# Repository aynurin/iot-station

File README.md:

# Nour Eggboard

This is a main board of a low-power battery powered IoT device controller based on ESP8266 (ESP-WROOM-02) that drives peripheral devices on I2C bus.

Currenly the project is under development and you can help in the following way:

* Suggest new features and report bugs
* Submit pull requests
* Help fund the development by [donating via PayPal](https://www.paypal.com/donate?business=M5DEYMX2BZ4MJ&no_recurring=0&item_name=Help+support+Nour+Eggboard+development&currency_code=USD)

## LICENSE

Currently this project is licensed as  [GNU AGPLv3](./LICENSE). This is intended to be changed to Apache or MIT when I get a better feel of the project and see how it moves forward. I would accept suggestions of a qualified lawyer as I need help figuring out how to move forward.

## How is this helpful

Most prototyping boards are exactly what they say - designed for prototyping and difficult to apply in a production device or if you are a hardcore hobbyist. Unlike those projects, the Eggboard is intended to be a final solution that lets you hook your peripherals to an I2C bus and enjoy a low-power battery operation, wireless charging, and WiFi connectivity out of the box.

Features:

* WiFi capability via ESP8266
* Own I2C port that allows I2C communication, sleep power line, ability to operate when host sleeps, and a host wakeup channel
* Customizable (via resistance change) sleep timer that drives the host and all of the peripherals
* Battery operation
* Wireless and USB-C charging
* USB-C programming via esptool or Arduino IDE (and other compatible IDEs and methods)

## Nour Egg Plant station

The example implementation is a Nour Egg plant ecosystem controller that is under development. This device is going to be commercially available for purchase in 2022 along with free downloadable app and a cloud-based analytics platform.

Key features of the Nour Egg:

* Monitor air quality, soil moisture, and lighting conditions of your home plant
* Low-power operation that runs for months on a single charge, and wireless charging
* WiFi connectivity to report statistics to the cloud and Nour Egg app
* Appealing look and feel in a nice shell and beautiful RGB light indicators

Implemented peripherals:

* Soil moisture sensor based on capacitance sensing using a coplanar capacitor probe
* Air quality sensor
* Light sensor
* LED indicators board driving 18 leds or 6 RGB leds

## Roadmap

The versioning works by bird names, e.g. see [WhatBird.com NA Birds by Size](https://www.whatbird.com/browse/attribute/birds_na_147/51/Size/):

| Milestone | Release Date | Focus |
|---|---|---|
| [Pine Siskin](https://github.com/aynurin/iot-station/milestone/1) | September 2021 | Hardware design |
| [Pygmy Nuthatch](https://github.com/aynurin/iot-station/milestone/2) | December 2021 | PoC Cloud and App |
| [Winter Wren](https://github.com/aynurin/iot-station/milestone/3) | March 2022 | Production feasible enclosure |
| [Hutton's Vireo](https://github.com/aynurin/iot-station/milestone/4) | June 2022 | Production feasible hardware, test board production |
.

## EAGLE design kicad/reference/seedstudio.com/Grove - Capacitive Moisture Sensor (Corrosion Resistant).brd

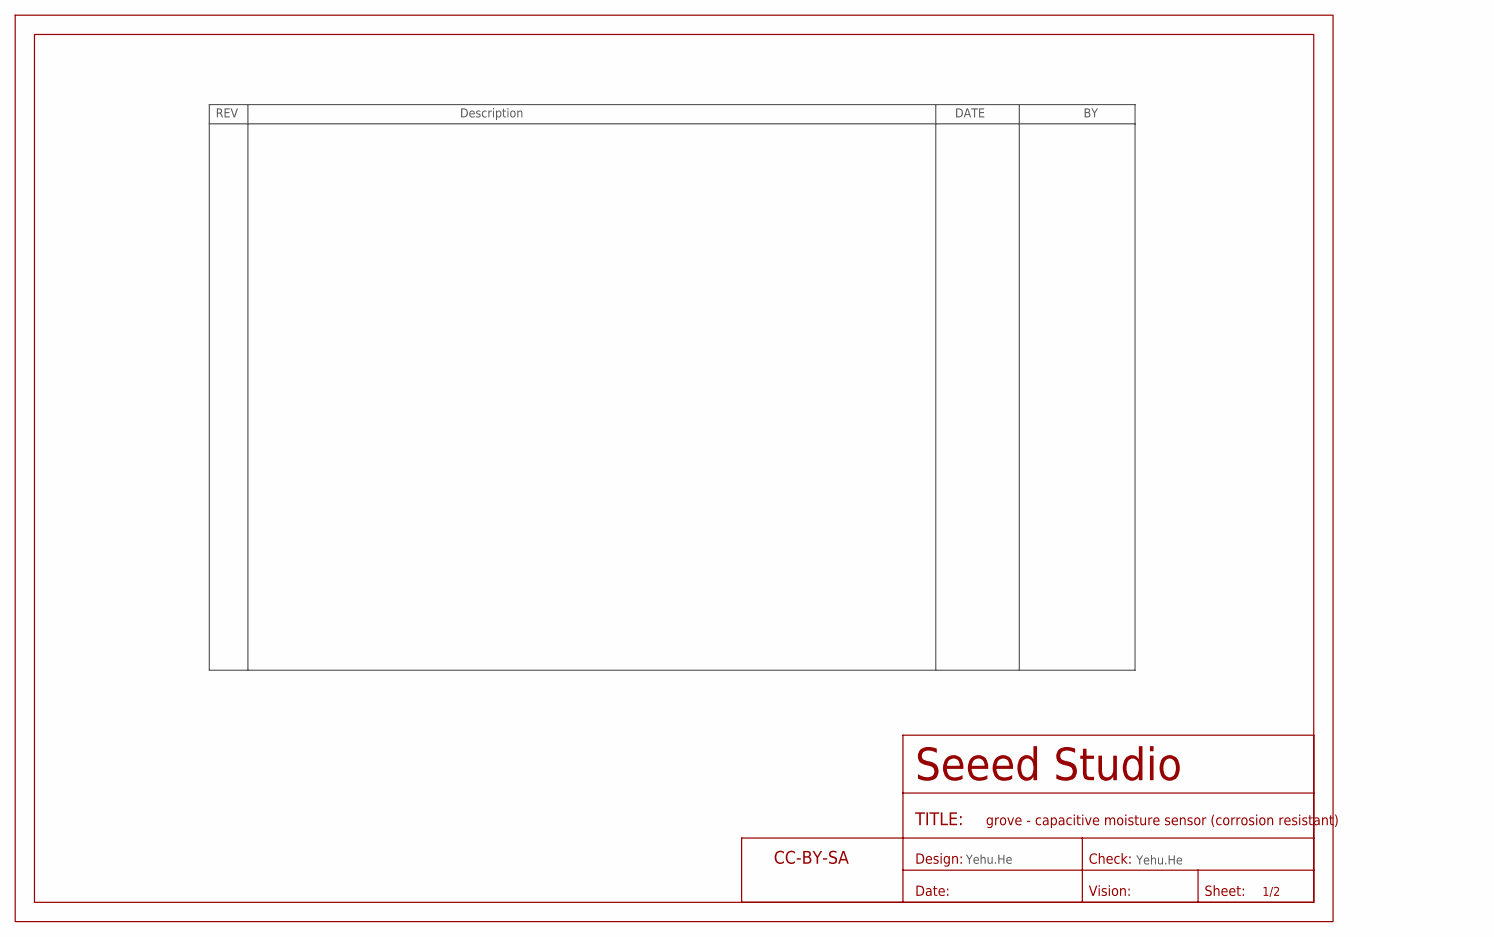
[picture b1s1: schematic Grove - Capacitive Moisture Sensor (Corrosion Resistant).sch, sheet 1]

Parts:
FR1: SEEEDSTUDIO-OPEN-SCH-FRAME; SEEEDSTUDIO-PCB-FRAME

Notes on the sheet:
Yehu.He

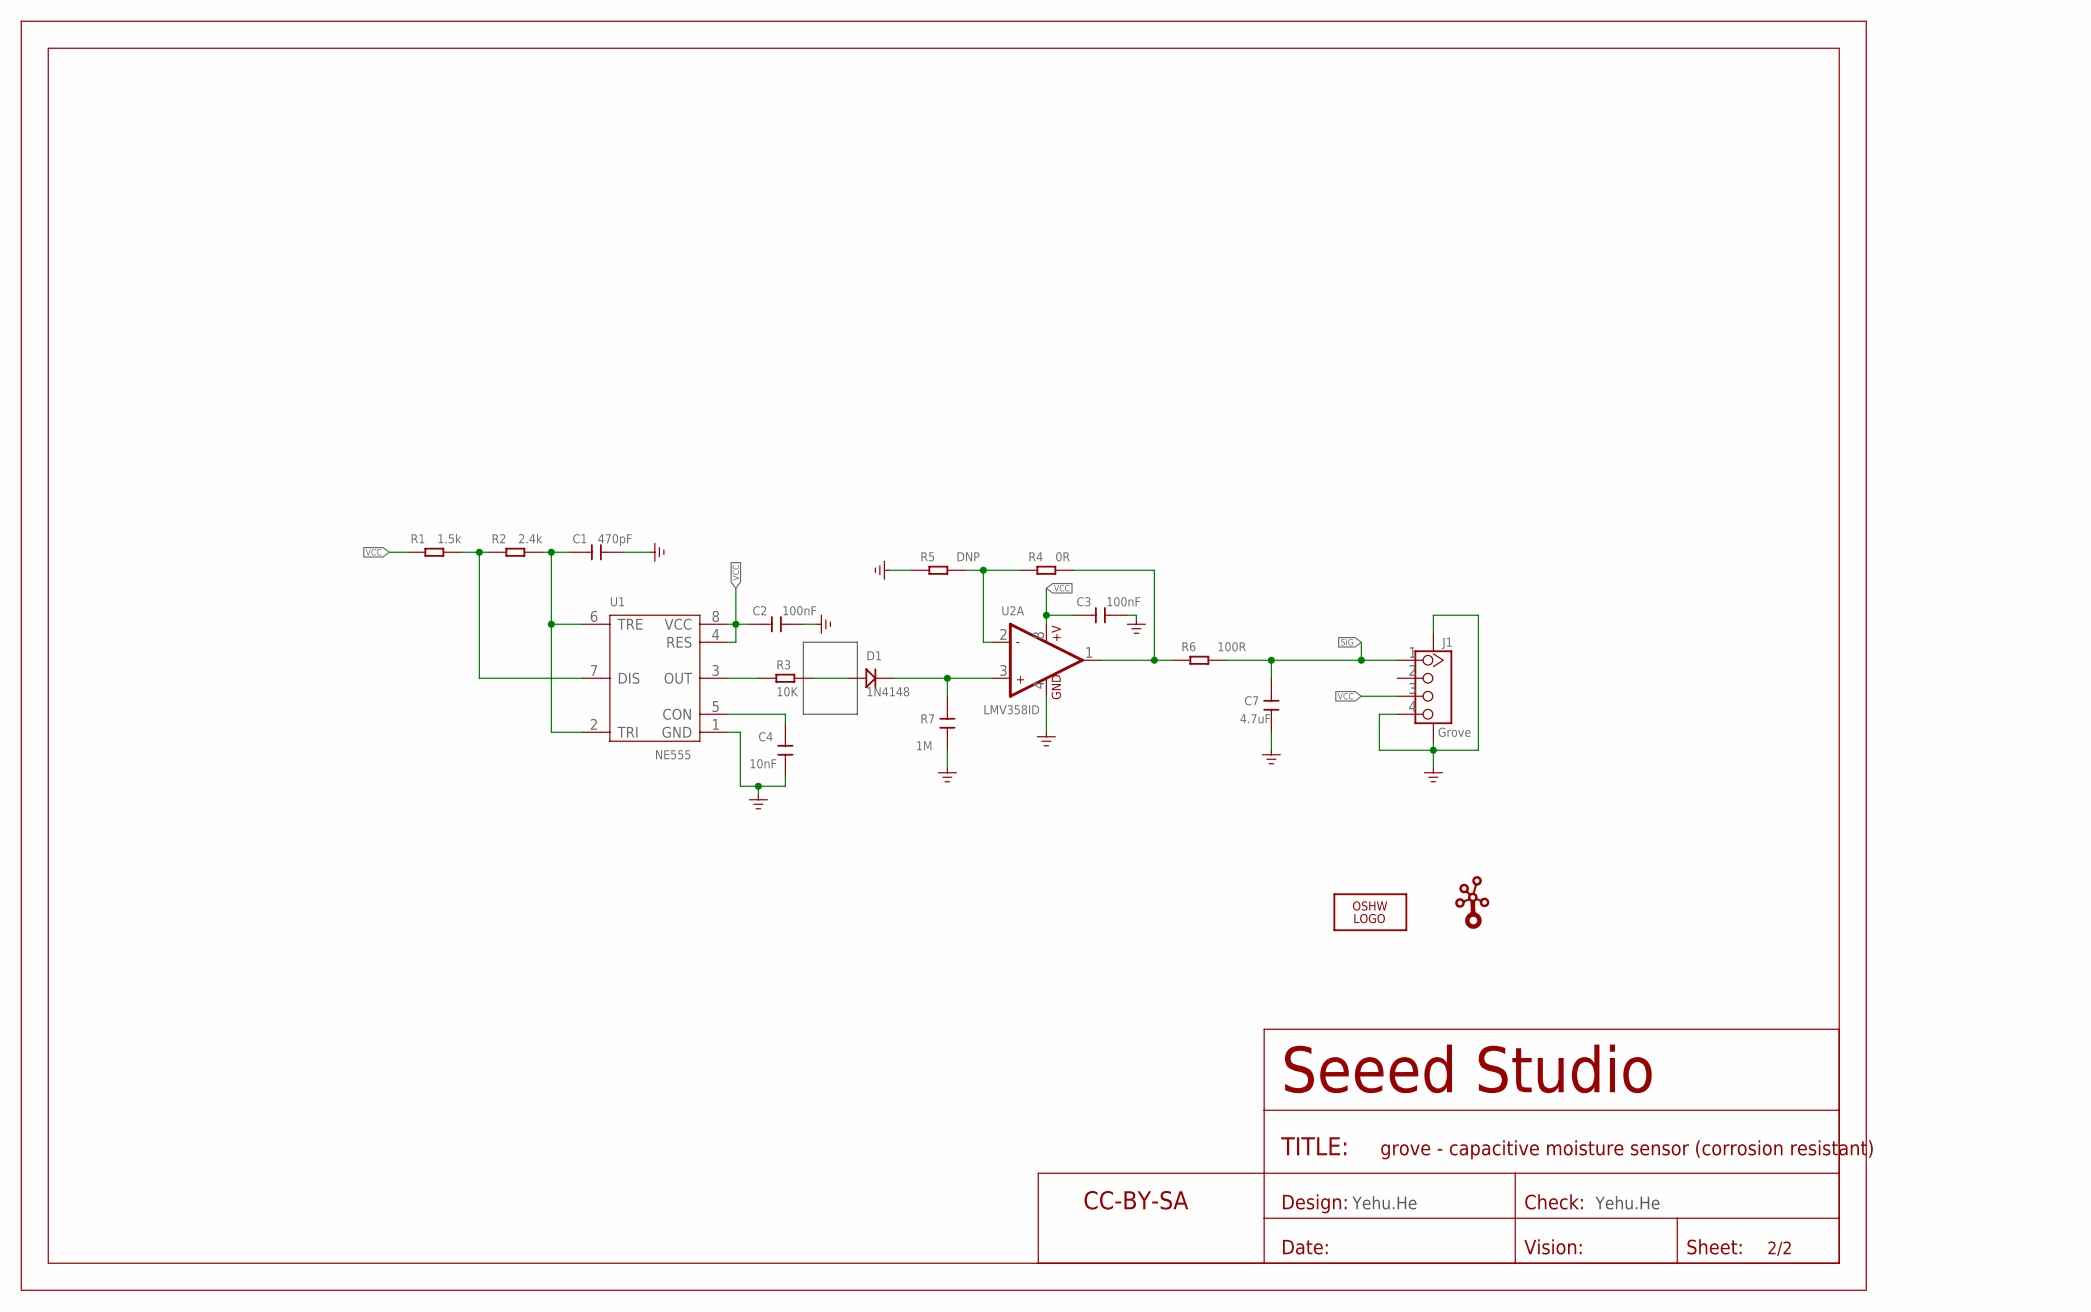
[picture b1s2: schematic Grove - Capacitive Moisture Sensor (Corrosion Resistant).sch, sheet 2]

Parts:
C1: 470pF; C0603
C2, C3: 100nF; C0603
C4: 10nF; C0603
C7: 4.7uF; C0603
D1: 1N4148; LL-34
FR2: SEEEDSTUDIO-OPEN-SCH-FRAME; SEEEDSTUDIO-PCB-FRAME
J1: Grove; HW4-SMD-2.0-90D
LOGO1: LOGO-OSHW-FILLX0200-NT; OSHW_FILLX200_NOTEXT
R1: 1.5k; R0603
R2: 2.4k; R0603
R3: 10K; R0603
R4: 0R; R0603
R5: DNP; R0603
R6: 100R; R0603
R7: 1M; C0603
U1: NE555; SOIC8-1.27-5X4MM
U2: LMV358ID; SOIC8-1.27-5X4MM
U$7: LOGO-GROVE; GROVE-SILK-BIG

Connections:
GND: C1.1, C2.1, C3.1, C4.2, C7.2, J1.4, J1.SS1, J1.SS2, R5.1, R7.2, U1.1 (GND), U2.4 (GND)
unnamed: R1.1, R2.2, U1.7 (DIS)
unnamed: C1.2, R2.1, U1.2 (TRI), U1.6 (TRE)
unnamed: C4.1, U1.5 (CON)
unnamed: R3.1, U1.3 (OUT)
unnamed: D1.A (+), R3.2
unnamed: D1.C (-), R7.1, U2.3 (+IN1)
unnamed: R4.1, R5.2, U2.2 (-IN1)
unnamed: R4.2, R6.1, U2.1 (OUT1)
SIG: C7.1, J1.1, R6.2
VCC: C2.2, C3.2, J1.3, R1.2, U1.4 (RES), U1.8 (VCC), U2.8 (+V)

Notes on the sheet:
Yehu.He

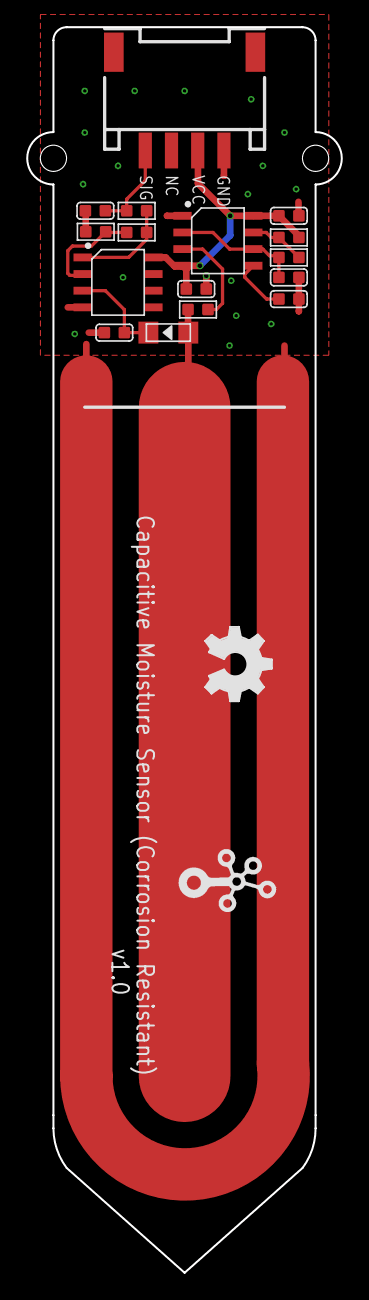
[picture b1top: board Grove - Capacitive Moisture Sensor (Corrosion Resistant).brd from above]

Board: 2 copper layers, 24.0 x 95.0 mm, 20 parts (0 on the bottom side), 11 nets.

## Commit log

2020-05-23 CCS811 wired and reading
2020-05-25 Sending data to Azure
2020-06-03 Initial refactoring to organize code
2020-06-04 Remapped I2C pins to D3 and D1 to release a PWM pin
2020-06-07 Soil moisture sensor
2020-06-15 KiCad draft
2020-06-16 Added GND and 3V3 areas and tracks to connect NodeMCU
2020-06-19 PCB 0.1 sent to production
2020-07-03 Scheme v.2 wired up
2020-07-10 Board v.2 sent for printing
2020-07-28 Started working on v3 - added ADC081 driver and removed CAP and IQS chips
2020-08-12 v3 schematics complete, USB breakout PCB designed
2020-08-12 v3 PCB in progress. Need to move LED driver to LEDs board and make it connect using the standard interface
2020-08-13 Moved the LED driver to LEDs board, refactored connectors. Hopefuly PCBNEW could update it all in place
2020-08-14 LEDs board done via I2C bus
2020-08-18 Initial board layout complete
2020-08-30 pcb v3 sent to production and the first attempts to design the enclosure
2021-07-11 Pre-refactoring, diagnostics complete, timer not working properly
2021-07-24 project folder cleanup
2021-07-24 Roadmap
2021-07-24 Added Roadmap to README
2021-07-24 Create LICENSE
2021-07-24 Added licensing info
2021-07-24 Added milestone links
2021-07-24 USB Wiring updated to fix RSTb pull-up
2021-07-24 Added USB Charger Detection Specification (BCv1.2_070312)
2021-07-25 SPX3819 resistance calculator
2021-07-25 SPX3819 datasheet
2021-07-30 Libraries cleanup
2021-08-01 Charger initial wiring complete
2021-08-01 Schematics cleanup
2021-08-02 Comitting yesterday's leftovers
2021-08-03 Relabeled and completed ERC
2021-10-04 Mapped footprints, PCB in progress
2021-10-29 trying github dot

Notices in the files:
parts and their libraries:
moudle-new: This work is licensed under the Creative Commons Attribution 4.0 International License.
To view a copy of this license,visit:
http://creativecommons.org/licenses/by-sa/4.0
moudle-new: CC-BY-SA
